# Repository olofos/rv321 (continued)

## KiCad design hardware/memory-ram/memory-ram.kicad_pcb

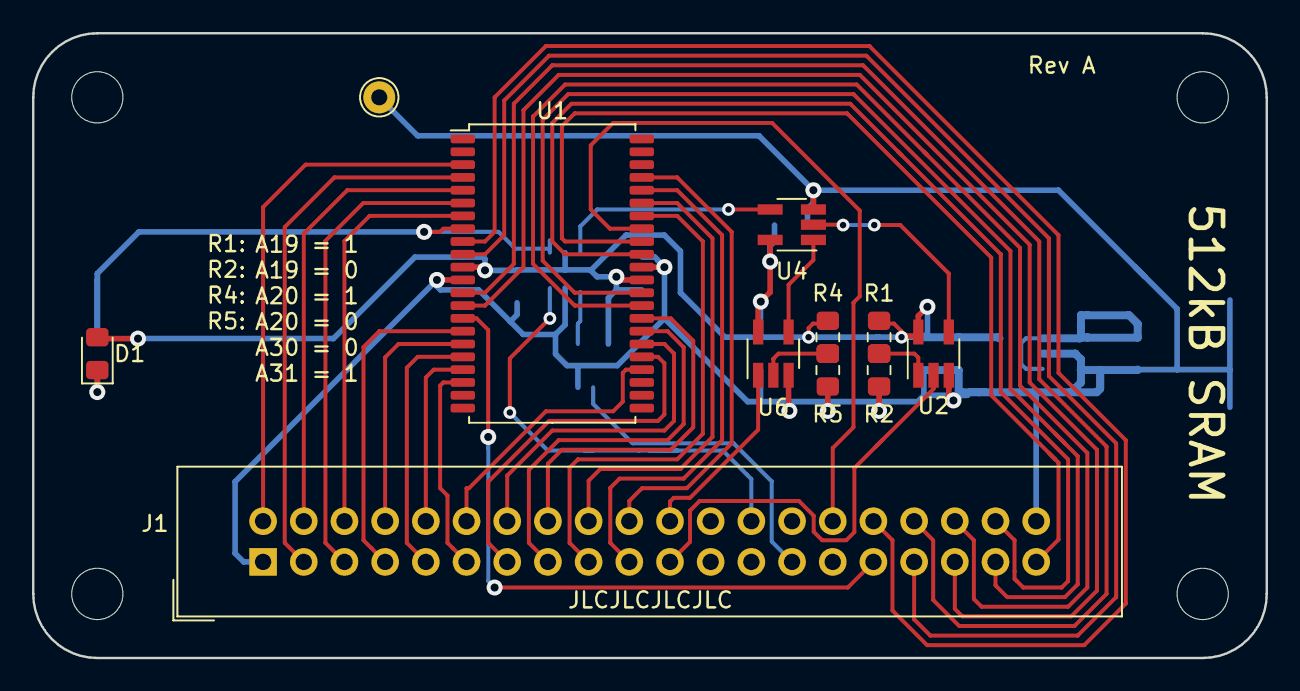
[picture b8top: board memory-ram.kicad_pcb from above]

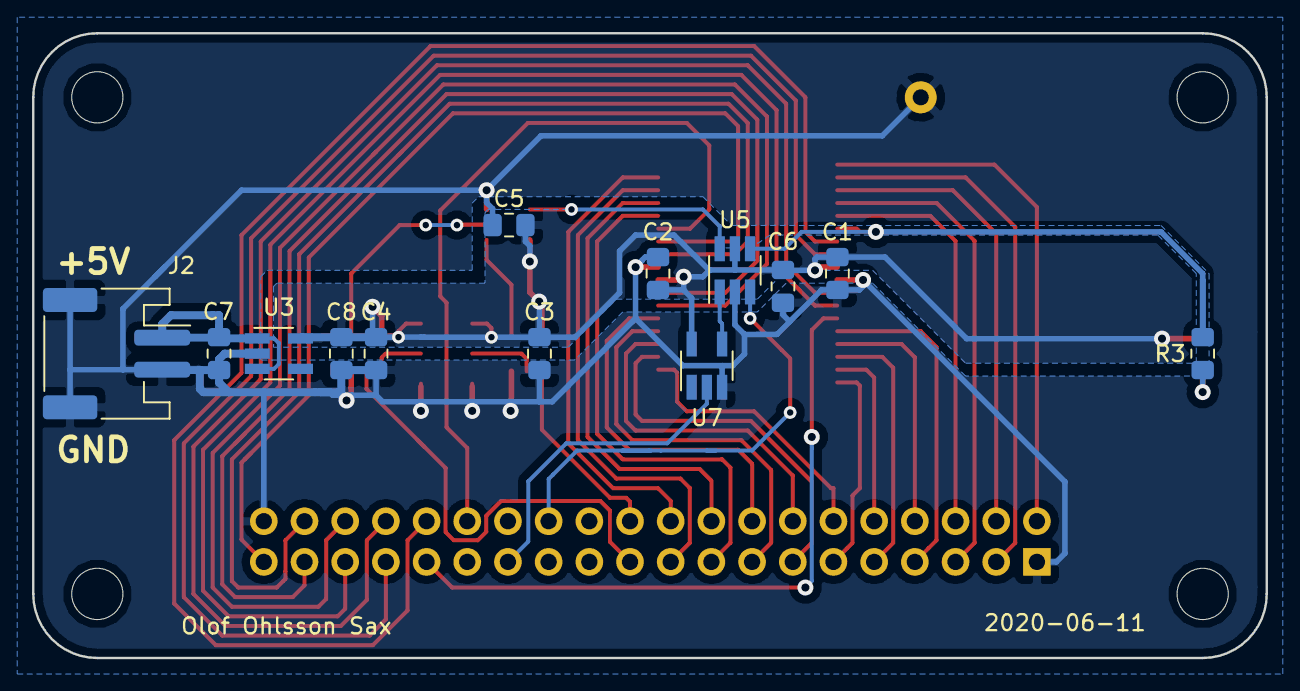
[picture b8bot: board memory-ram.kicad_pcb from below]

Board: 2 copper layers, 77.0 x 39.0 mm, 28 parts (13 on the bottom side), 44 nets.

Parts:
C1, C2, C3, C4, C5, C6: 100n; C_0805_2012Metric_Pad1.15x1.40mm_HandSolder
C7, C8: 1u; C_0805_2012Metric_Pad1.15x1.40mm_HandSolder
D1: LED; LED_0805_2012Metric_Pad1.15x1.40mm_HandSolder
H1, H2, H3, H4: MountingHole; MountingHole_3.2mm_M3
J1: Conn_Mem_Ext; IDC-Header_2x20_P2.54mm_Vertical
J2: Conn_Power; JST_PH_S2B-PH-SM4-TB_1x02-1MP_P2.00mm_Horizontal
R1, R2, R4, R5: 0; R_0805_2012Metric_Pad1.15x1.40mm_HandSolder
R3: 330; R_0805_2012Metric_Pad1.15x1.40mm_HandSolder
TP1: TestPoint; TestPoint_THTPad_D2.0mm_Drill1.0mm
U1: IS61WV5128EDBLL-10TLI; TSOP-II-44_10.16x18.41mm_P0.8mm
U2, U6: 74LVC1G86; SOT-23-5_HandSoldering
U3: MIC5504-3.3YM5; SOT-23-5_HandSoldering
U4: 74LVC1G32; SOT-23-5_HandSoldering
U5: 74LVC1G332; SOT-23-6_Handsoldering
U7: 74LVC1G04; SOT-23-5_HandSoldering

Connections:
/A0: J1.2, U1.3
/A1: J1.3, U1.4
/A2: J1.4, U1.5
/A3: J1.5, U1.6
/A4: J1.6, U1.7
/A5: J1.7, U1.16
/A6: J1.8, U1.17
/A7: J1.9, U1.18
/A8: J1.10, U1.19
/A9: J1.11, U1.20
/A10: J1.12, U1.26
/A11: J1.13, U1.27
/A12: J1.14, U1.28
/A13: J1.15, U1.29
/A14: J1.16, U1.30
/A15: J1.17, U1.38
/A16: J1.18, U1.39
/A17: J1.19, U1.40
/A18: J1.20, U1.41
/A19: J1.21, U2.2
/A19-20: U4.4, U5.6
/A20: J1.22, U6.1
/A30: J1.26, U5.3
/A31: J1.27, U7.2
/B19: R1.2, R2.1, U2.1
/B20: R4.2, R5.1, U6.2
/D0: J1.32, U1.9
/D1: J1.33, U1.10
/D2: J1.34, U1.13
/D3: J1.35, U1.14
/D4: J1.36, U1.31
/D5: J1.37, U1.32
/D6: J1.38, U1.35
/D7: J1.39, U1.36
/V_IN: C7.2, J2.1, U3.1, U3.3
/X19: U2.4, U4.2
/X20: U4.1, U6.4
/~A31: U5.1, U7.4
/~CE: R3.2, U1.8, U5.4
/~MEM_OE: J1.30, U1.37
/~MEM_WE: J1.31, U1.15
GND: C1.1, C2.1, C3.1, C4.1, C5.1, C6.1, C7.1, C8.1, J1.1, J1.40, J2.2, J2.MP, R2.2, R5.2, TP1.1, U1.12, U1.34, U2.3, U3.2, U4.3, U5.2, U6.3, U7.3
unnamed: D1.1, R3.1
VCC: C1.2, C2.2, C3.2, C4.2, C5.2, C6.2, C8.2, D1.2, R1.1, R4.1, U1.11, U1.33, U2.5, U3.5, U4.5, U5.5, U6.5, U7.5

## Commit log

2020-01-21 Initial import of simulation blocks
2020-01-21 Make ALU 32 bit
2020-01-25 Working basic CPU
2020-03-12 Basic (almost) working CPU
2020-03-12 Add updated components
2020-03-13 Fixed signal/pin names and tests
2020-03-14 Added tests
2020-03-17 Cleaned up circuit
2020-03-17 Marked currently failing tests
2020-03-17 Further estetic cleanup
2020-03-19 Remove step len 32
2020-03-19 Reimplement ALU-shift-step state machine
2020-03-19 Remove len=32 from substep counter
2020-03-19 Add one more bit to step counter
2020-03-19 Changed length counter
    New values:
    0 0 Len 1, last step
    0 1 Len 1, bus disabled
    1 0 Len 1, bus enabled
    1 1 Len 8, bus enabled
2020-03-19 Reordering of microcode signals
2020-03-20 Introduce ALU_AUX signal
    Used as a combination of ALU_FLAG_LATCH and ALU_SHIFT_STEP_EN
2020-03-20 Fix bug in SRL and SRA when shift amount has more than 5 bits
2020-03-20 Replace Const1 and Const31 immediates with hardcoded high
2020-03-20 Fix bug in JAL and JALR
2020-03-22 Implement fence and fence.i as nop
2020-03-22 Reset ADDR_LATCH at first opportunity
2020-03-23 Implemented basic CSR instructions
2020-04-08 Implement CSRs
2020-04-08 Basic interrupt controller
2020-04-08 Add CRSs and interrupt controller
2020-04-08 Added .gitignore
2020-04-08 Added support for illegal instruction trap
2020-04-09 Fix bug in J-type immidiate
2020-04-12 Make MTVEC settable
2020-04-12 Fix bug in MCAUSE
2020-04-13 Cleanup
2020-04-13 Refactored memory circuit
2020-04-13 Fix bug in mscratch
2020-04-13 Refactor ALU
2020-04-14 Cleanup of debug console
2020-04-14 More cleanup
2020-04-14 Fix Address latch signal for load instructions
2020-04-14 Better margin when latching address for load
2020-04-14 Change steplen 8 to steplen 4
2020-04-14 Optimise load and store address increments
2020-04-14 Take advantage of steplen 4
2020-04-14 Add support for wait states
2020-04-14 Improve layout
2020-04-14 Single step instruction until op-latch
2020-04-14 Use single instruction input for breakpoint
2020-04-14 Optimised store instructions
2020-04-15 Save three pins by driving shift step clock directly
    This loses one clock cycle for shift instructions
2020-04-16 Get rid of ADDR_PE signal
    Replace with flipflop copying ADDR_LATCH on CLK
2020-04-17 Remove PC_CNT_PE signal
2020-04-18 Reordered microcode control signals
2020-04-19 Reorder microcode address bits
2020-04-19 Cleaned up PC
2020-04-19 Add count by two option to PC
2020-04-30 Introduce ImmMux to lower the number of long traces
2020-04-30 Updated ALU tests
2020-04-30 Replace 4->1 mux by two 2->1 muxes
2020-04-30 Add missing subcircuit
2020-05-04 Fix bug in nop!
2020-05-04 Add basic support for compressed instructions
    Instruction mapping tables from https://github.com/artlav/riscv-c2g-table/blob/master/riscv_c2g_lut_c2.h
2020-05-09 Updated mem tests
2020-05-09 Renamed LEN4 to ~LEN4
2020-05-13 Added start of test parser
2020-05-13 Added moew misformed statements to test
2020-05-14 Renamed tests
2020-05-14 Add extra tests and clean up coverage testing
2020-05-14 Export tokenizer_ ... _read_char, _unread_char and _read_char_raw
2020-05-14 Added reallocate
2020-05-15 Fixed typo in test setup
2020-05-15 Improved error reporting
2020-05-15 Parse file header
2020-05-15 Make function static
2020-05-15 Check that pin numbers are in range
2020-05-15 Add missing tests
2020-05-15 Added more invalid statements to test
2020-05-15 Removed unreachable code
2020-05-15 Remove unused expression types
2020-05-15 Parse multiple statements
2020-05-15 Avoid printing an error when finding an end token
    We should print an error if we are not in a loop...
2020-05-15 Keep track of statement line numbers
2020-05-15 Remove debug output
2020-05-15 Parse whole files
2020-05-15 Add missing object file
2020-05-16 Wrap fopen and fclose in tests
2020-05-16 We don't need to actually define a function to test parsing
2020-05-16 Cleaned up test output
2020-05-16 allocate aborts on error
2020-05-16 We don't need to export parse_test_file
2020-05-16 Make parse_test_file static
2020-05-16 Fix memory leak on error
2020-05-16 Add tests for parser.c
2020-05-16 Add missing file
2020-05-17 Further improved test output
2020-05-18 Evaluate expressions
2020-05-18 Slightly better test reporting
2020-05-19 Added missing header file
2020-05-19 Rename tests
2020-05-19 Replace clock gate with flip flop
2020-05-20 Wait as long as ~{WAIT} is pulled down
2020-06-10 ALU schematic and pcb
2020-06-10 Logo footprints
2020-06-10 Register schematic and PCB
2020-06-10 PC schematic and PCB
2020-06-10 Memory controller schematic and PCB
2020-06-10 SRAM schematic and PCB
2020-06-10 Power splitter schematic and PCB
2020-06-10 Flash schematic and PCB
2020-06-10 Test bench schematic and PCB
2020-06-10 Change default value of ADDR_PE
2020-06-10 Add simple main for testing parser
2020-06-10 Memory does not use ~CLK
2020-06-10 Added simple test
2020-06-10 Added ~RESET to memory bus
2020-06-11 Unified footprints
2020-06-12 Added kicad project files
2020-06-12 Fully connect test headers
2020-06-12 Added filters for kicad .sch and .pro files
2020-06-12 Add more missing kicad files
2020-06-12 Added 3d model
2020-06-12 Remoce 3d model of unpopulated components
2020-06-16 Give ops to plot on the command line
2020-06-16 Updated test
2020-06-16 Added generated test
2020-06-18 Added placeholders for JLCPCB serial numbers
2020-06-18 Saved plot settings
2020-06-19 Added test points
2020-06-20 Add J-LINK 10-pin SWD header
2020-06-20 Fix SWD pinout
2020-06-21 Generate gerbers
2020-06-22 Added resistors to some unused pins and a logo
2020-11-06 Updated linker script for tests
2020-11-06 Make CSR_ADDR_LATCH default to 1
2020-11-06 Improve formatting of signals
2020-11-06 Fix main test file
2020-11-06 Minor fixes to simulated circuit
2020-12-09 Fix C.JAL instruction
2020-12-09 Directly control PC_OUT_LATCH instead of _SP
    JAL can now be implemented by getting the address of the next
    instruction from the PC counter. This allows us to support C.JAL
2020-12-17 Added basic emulator
2020-12-17 Remove dead code
2020-12-21 Use inline initialization
2020-12-21 Add LCD display
    HD44780 emulator from https://github.com/visrealm/vrEmuLcd
2020-12-21 Hide LCD window until first write
2020-12-27 Fix STM32G0 pin function
2020-12-27 Added warning about switched SWDIO and SWCLK to schematic
    Should be fixed in rev B
2020-12-29 Added signal breakout board for testing
2020-12-30 Updated layout
2020-12-31 Change testpoints to pin header
2021-01-23 Finished layout
2021-01-23 Updated opcode tests
2021-01-23 Slightly improved LCD simulator
2021-01-23 Added draft of README
2021-02-12 Remove extra ADDR_CLK cycle in LB and LH
2021-02-12 Parse args and highlight signals
2021-02-12 Test #if USE_LCD instead of #ifdef USE_LCD
2021-02-17 Updated in-/output of registers in simulation to match real circuit
2021-02-17 Move address decoding to main circuit of simulator
2021-02-18 Fix integer overflow for random(1)
2021-02-18 Read pins in chip-bank-pin (eg 1A4) format
2021-02-18 Remove extra newline in error messages
2021-02-19 Support skipped bits in pin definition
2021-02-19 Improved tests for header parser
2021-02-20 Add pullup flag to signals
2021-02-20 Add extra test to eval_expr
2021-02-28 Removed C implementaion of test-runner
2021-02-28 Added basic python implementation of test runner
2021-03-29 Reogranised test runner into a module
2021-03-29 Moved test runner code
2021-03-29 Added test bench firmware
2021-04-20 Introduce 16-bit SPI functions
2021-04-20 Let mcp2317 driver work with 16 bit data
2021-04-20 Add uart_puts
2021-04-20 Use 16-bit interface
2021-04-20 Use uart_puts
2021-04-20 Add functions to turn console echo on/off
2021-04-20 Remove commented out code
2021-04-20 Add function ite
2021-04-20 Add needs_input
2021-04-20 Import file instead of load to avoid name clash
2021-04-20 Check if args.highlight is set before using it
2021-04-20 Updated tests
2021-04-20 Add support for initial opcode
2021-04-20 Add some new components
2021-04-21 Don't increase address beyond end of compact instruction
2021-04-21 Fix USE_LCD and add TEST_BRIEF for quicker test
2021-04-23 Add signal IMM_PC_OUT_SP
2021-04-23 Renamed signals-new.py to signals.py
2021-04-23 Fetch at the end of each instruction
2021-09-02 Sign bit is D7. Change 74LVC1G38 to 74LVC1G00
2021-09-03 Fixed LED latch
2022-01-21 Added errata to pc schematic
2022-01-21 Added errata to ROM schematic
2022-01-21 Optimized microcode and timing circuit
2022-01-21 Added the commands "read-iodir" and "read-pullup" to the testbench firmware
2022-01-21 Comment out test code for now
2022-01-21 Enable pullups by default
2022-01-21 Updated test runner
2022-01-21 Correct PC connector
2022-01-21 Add updated caches
2022-01-21 Add test circuit for SPI
2022-01-21 Make file paths relative
2022-01-22 Rev B of memory-rom: switch OE and CE
2022-01-22 Updated gerber settings
2022-01-22 Add revision number to the front silk screen
2022-01-22 Added test bench link file
2022-01-22 Updated gitignore
2022-01-24 Added microcode editor
2022-01-24 Added draft for IO pcb
2022-01-24 Added draft of LCD pcb
2022-01-24 Added missing lib tables
2022-01-24 Update lib tables
2022-01-24 Added missing client files
2022-01-24 Removed counter example component
2022-01-24 Build microcode app using docker
2022-01-24 Added simple scripts to build and run microcode app
2022-01-25 Added simple exit button
2022-01-25 Nicer run bat file
2022-01-26 Unify MRET/TRAP
2022-01-26 Unify MRET and TRAP
2022-01-27 Added 74LVC1G27
2022-01-27 74LVC1G27 should be a nor gate
2022-01-27 Decode LR.W and SC.W
2022-01-28 Revert "Decode LR.W and SC.W"
    This reverts commit bcef8c9c397fee6a618aa3a6d0661a33eaf844c4.
    We will emulate these instructions in software if they are needed.
2022-06-08 Move Imm Mux inside opcode circuit
2022-06-08 Keep OP_LATCH_LSB high until OP_LATCH goes low
2022-06-08 Gate CNT-2 on OP_LATCH_LSB
    Todo: invert ADDR_CLK
2022-06-08 Invert ADDR_CLK
2022-06-08 And plus not gate replaced with nand
2022-06-08 Added start of opcode pcb
2022-06-08 Added registers pcb
2022-06-08 Added missing lib table files
2022-06-14 Improved clock circuit
2022-06-14 Load main test firmware
2022-06-14 Fix interrupt mechanism
2022-06-14 First instruction should be jalr x0, 0(x0)
2022-06-14 A little microcode documentation
2022-06-16 Remove unnecessary diodes
2022-06-16 Cleanup circuit
2022-06-17 Update all to Kicad 6
2022-06-17 Ignore gerber files
2022-06-20 Updated .gitignore
2022-06-20 Invert SLEEP in microcode
2022-06-20 Actually add inverted SLEEP signal...
2022-06-20 Invert SLEEP and WAKEUP
2022-06-27 Make IMM_PC_OUT_PC a generated signal.
2022-06-28 Started clock circuit and PCB
2022-06-30 Updated schematics and pcbs
2022-06-30 Corrected minor mistakes in circuit
2022-07-09 Updated PCBs
2022-07-10 Added two LEDs
2022-07-13 Added simulation of timer circuit
2022-07-22 Updated opcode and step counter PCBs
2022-07-22 Start of memory mapped timer circuit
2022-09-07 Added comments to JAL/JALR
2022-09-07 Added start of adapter circuits
2022-09-07 Reorganised simulation circuit
2022-09-07 Added Jumper footprint
2022-09-07 Updated symbol library
2022-09-08 Derive IMM_LATCH from OP_LATCH
2022-09-08 Add comments to microcode
2022-09-08 Repeat the last microcode step op each instruction
2022-09-12 Generate OP_LATCH and ADDR_CLK in hardware
2022-09-12 Remove ADDR_CLK from microcode
2022-09-12 Change step length 4 to step length 8
2022-09-14 Updated cycle count in simulator
2022-09-26 Fix interrupt controller
2022-10-06 Add ADDR_CLK and ~ADDR_PE to microcode view
2022-10-17 Fix microcode for shift instructions
2022-10-19 Added TODO comments
2022-10-19 Support 32 registers
2022-10-19 Start separating MRET and TRAP
2022-10-25 Added OP_LATCH and IMM_LATCH to editor
2022-10-27 Added ROM + programming adapter PCBs
2022-11-07 Use custom components for simulation
